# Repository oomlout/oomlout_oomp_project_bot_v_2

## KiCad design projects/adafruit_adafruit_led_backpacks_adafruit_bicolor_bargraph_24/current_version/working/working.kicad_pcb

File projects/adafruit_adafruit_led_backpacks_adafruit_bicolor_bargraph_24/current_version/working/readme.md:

# adafruit_led_backpacks
 
## summary 
* id: adafruit_adafruit_led_backpacks_adafruit_bicolor_bargraph_24
* user: adafruit
* name: adafruit_led_backpacks
* board: adafruit_bicolor_bargraph_24
* repo: https://github.com/adafruit/Adafruit-LED-Backpacks

* src_file_repo_sch: 
* src_file_repo_sch_link: https://github.com/adafruit/Adafruit-LED-Backpacks/tree/master/
* full details link: https://github.com/oomlout/oomlout_oomp_project_bot_v_2/tree/main/projects/adafruit_adafruit_led_backpacks_adafruit_bicolor_bargraph_24/current_version/working  

## schematic  
  
[schematic (pdf)](working_schematic.pdf) 

## pcb  

[board (pdf)](working.pdf)  

## working_bom
| Id | Designator | Footprint | Quantity | Designation | Supplier and ref |  | None | 
| --- | --- | --- | --- | --- | --- | --- | --- | 
| 1 | JP1 | 1X05_ROUND_70 | 1 |  |  |  | [''] | 
| 2 | D1,D3 | SOD-323F | 2 | CUS530 |  |  | [''] | 
| 3 | A0,A1,A2 | SOLDERJUMPER_REFLOW_NOPASTE | 3 |  |  |  | [''] | 
| 4 | R4,R3,R5,R6 | 0603-NO | 4 | 47K |  |  | [''] | 
| 5 | U$2,U$1 | FIDUCIAL_1MM | 2 | FIDUCIAL |  |  | [''] | 
| 6 | U2 | SOP28_300MIL_SKINNY | 1 | HT16K33 |  |  | [''] | 
| 7 | U$6,U$7 | STEMMAQT | 2 |  |  |  | [''] | 
| 8 | @HOLE0,@HOLE2,@HOLE3,@HOLE1 |  | 4 |  |  |  | [''] | 
| 9 | R2,R1 | 0603-NO | 2 | 10K |  |  | [''] | 
| 10 | U$3 | ADAFRUIT_5MM | 1 |  |  |  | [''] | 
| 11 | CONN1,CONN2 | JST_SH4_RA | 2 | STEMMA_I2C_QTRA |  |  | [''] | 
| 12 | D2 | CHIPLED_0603_NOOUTLINE | 1 | GREEN |  |  | [''] | 
| 13 | C1 | 0805-NO | 1 | 10uF |  |  | [''] | 
| 14 | LEDJMP0 | SOLDERJUMPER_CLOSEDWIRE | 1 |  |  |  | [''] | 
| 15 | U$8 | PCBFEAT-REV-040 | 1 |  |  |  | [''] | 
| 16 | LED1,LED2 | SEGMENT_STARTBUST_DUAL_KWA-541CBB | 2 |  |  |  | [''] | 

## bom_schematic
| Ref | Qnty | Value | Cmp name | Footprint | Description | Vendor | DNP | 
| --- | --- | --- | --- | --- | --- | --- | --- | 
| A0, A1, A2 | 3 | SOLDERJUMPERREFLOW_NOPASTE | SOLDERJUMPERREFLOW_NOPASTE | working:SOLDERJUMPER_REFLOW_NOPASTE |  |  |  | 
| C1 | 1 | 10uF | CAP_CERAMIC0805-NOOUTLINE | working:0805-NO |  |  |  | 
| CONN1, CONN2 | 2 | STEMMA_I2C_QTRA | STEMMA_I2C_QTRA | working:JST_SH4_RA |  |  |  | 
| D1, D3 | 2 | CUS530 | DIODESOD-323F | working:SOD-323F |  |  |  | 
| D2 | 1 | GREEN | LED0603_NOOUTLINE | working:CHIPLED_0603_NOOUTLINE |  |  |  | 
| JP1 | 1 | HEADER-1X570MIL | HEADER-1X570MIL | working:1X05_ROUND_70 |  |  |  | 
| LED1, LED2 | 2 | DISP_SEGMENT_STARBURST_DUAL_COMMONCATHODE | DISP_SEGMENT_STARBURST_DUAL_COMMONCATHODE | working:SEGMENT_STARTBUST_DUAL_KWA-541CBB |  |  |  | 
| LEDJMP0 | 1 | SOLDERJUMPERCLOSED | SOLDERJUMPERCLOSED | working:SOLDERJUMPER_CLOSEDWIRE |  |  |  | 
| R1, R2 | 2 | 10K | RESISTOR_0603_NOOUT | working:0603-NO |  |  |  | 
| R3, R4, R5, R6 | 4 | 47K | RESISTOR_0603_NOOUT | working:0603-NO |  |  |  | 
| U2 | 1 | HT16K33 | HT16K33_SOP28_SKINNY | working:SOP28_300MIL_SKINNY |  |  |  | 
| U$1, U$2 | 2 | FIDUCIAL | FIDUCIAL | working:FIDUCIAL_1MM |  |  |  |

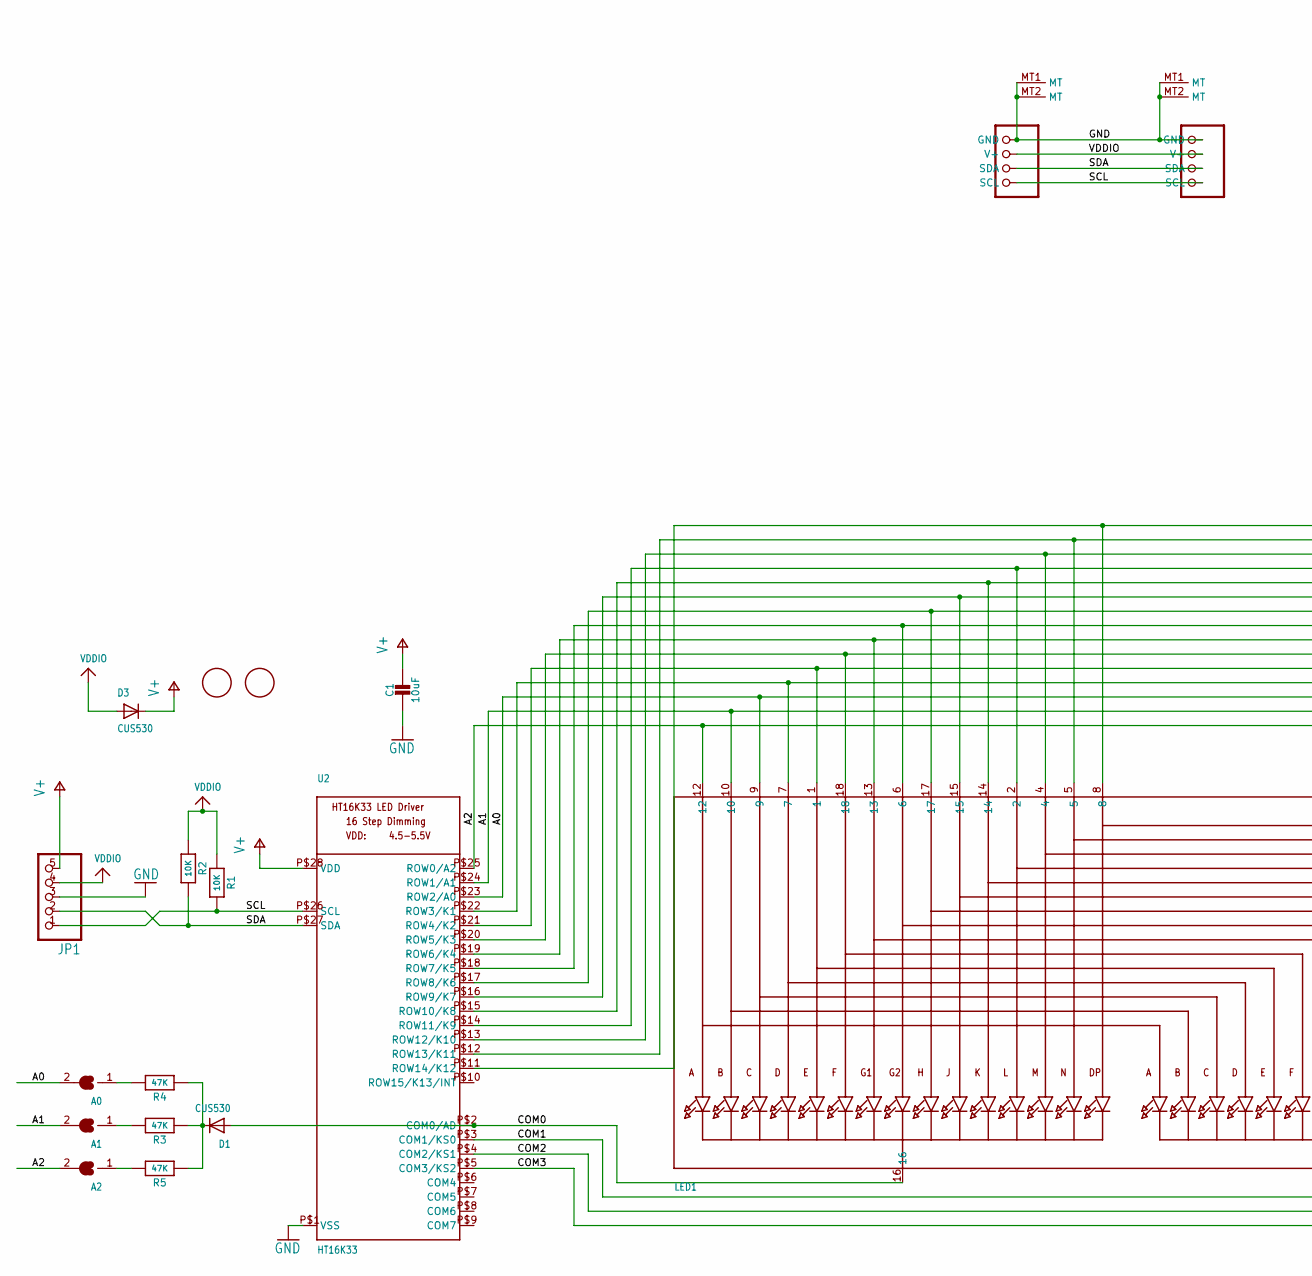
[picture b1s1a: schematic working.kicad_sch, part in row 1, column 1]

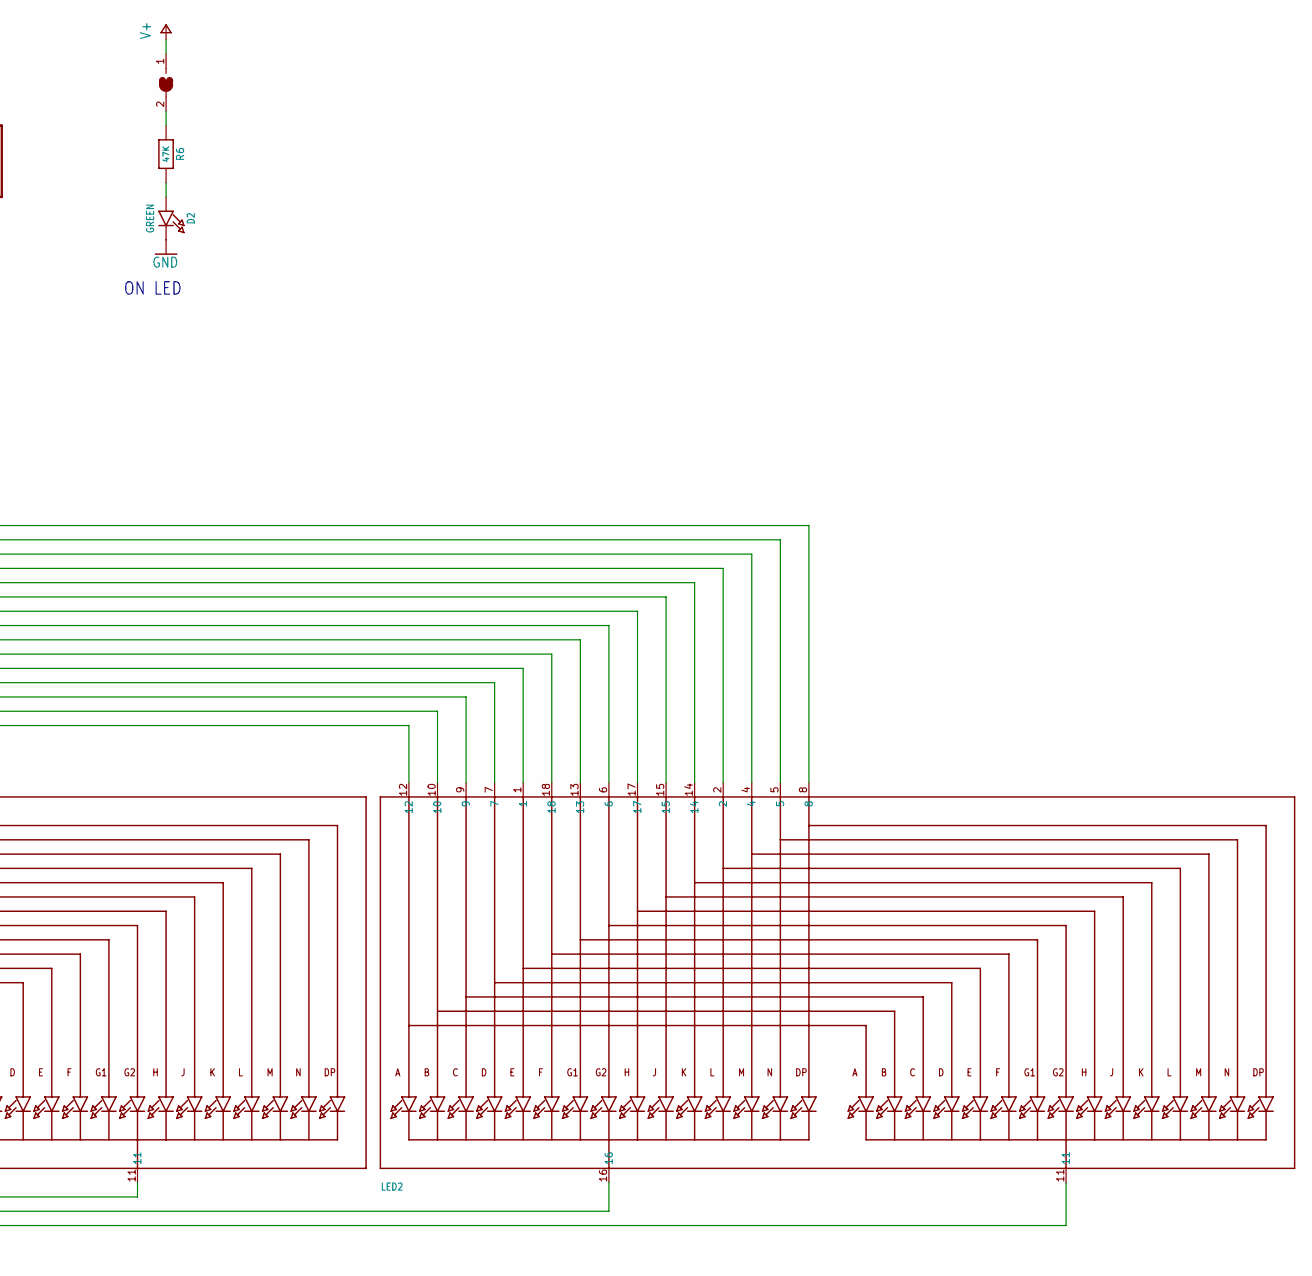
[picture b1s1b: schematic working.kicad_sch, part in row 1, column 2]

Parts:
A0, A1, A2: SOLDERJUMPERREFLOW_NOPASTE; SOLDERJUMPER_REFLOW_NOPASTE
C1: 10uF; 0805-NO
CONN1, CONN2: STEMMA_I2C_QTRA; JST_SH4_RA
D1, D3: CUS530; SOD-323F
D2: GREEN; CHIPLED_0603_NOOUTLINE
JP1: HEADER-1X570MIL; 1X05_ROUND_70
LED1, LED2: DISP_SEGMENT_STARBURST_DUAL_COMMONCATHODE; SEGMENT_STARTBUST_DUAL_KWA-541CBB
LEDJMP0: SOLDERJUMPERCLOSED; SOLDERJUMPER_CLOSEDWIRE
R1, R2: 10K; 0603-NO
R3, R4, R5, R6: 47K; 0603-NO
U2: HT16K33; SOP28_300MIL_SKINNY
U$1, U$2: FIDUCIAL; FIDUCIAL_1MM

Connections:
A0: A0.2, LED1.9, LED2.9, U2.P$23 (ROW2/A0)
A1: A1.2, LED1.10, LED2.10, U2.P$24 (ROW1/A1)
A2: A2.2, LED1.12, LED2.12, U2.P$25 (ROW0/A2)
COM0: D1.A, LED1.16, U2.P$2 (COM0/AD)
COM1: LED1.11, U2.P$3 (COM1/KS0)
COM2: LED2.16, U2.P$4 (COM2/KS1)
COM3: LED2.11, U2.P$5 (COM3/KS2)
GND: C1.2, CONN1.1 (GND), CONN1.MT1 (MT), CONN1.MT2 (MT), CONN2.1 (GND), CONN2.MT1 (MT), CONN2.MT2 (MT), D2.C, JP1.3, U2.P$1 (VSS)
unnamed: D1.C, R3.1, R4.1, R5.1
unnamed: D2.A, R6.2
unnamed: LED1.17, LED2.17, U2.P$17 (ROW8/K6)
unnamed: LED1.15, LED2.15, U2.P$16 (ROW9/K7)
unnamed: LED1.14, LED2.14, U2.P$15 (ROW10/K8)
unnamed: A2.1, R5.2
unnamed: LED1.2, LED2.2, U2.P$14 (ROW11/K9)
unnamed: LED1.4, LED2.4, U2.P$13 (ROW12/K10)
unnamed: LED1.7, LED2.7, U2.P$22 (ROW3/K1)
unnamed: LED1.1, LED2.1, U2.P$21 (ROW4/K2)
unnamed: LED1.18, LED2.18, U2.P$20 (ROW5/K3)
unnamed: LED1.13, LED2.13, U2.P$19 (ROW6/K4)
unnamed: LED1.5, LED2.5, U2.P$12 (ROW13/K11)
unnamed: LED1.8, LED2.8, U2.P$11 (ROW14/K12)
unnamed: LED1.6, LED2.6, U2.P$18 (ROW7/K5)
unnamed: LEDJMP0.2, R6.1
unnamed: A1.1, R3.2
unnamed: A0.1, R4.2
SCL: CONN1.4 (SCL), CONN2.4 (SCL), JP1.1, R1.2, U2.P$26 (SCL)
SDA: CONN1.3 (SDA), CONN2.3 (SDA), JP1.2, R2.2, U2.P$27 (SDA)
V+: C1.1, D3.C, JP1.5, LEDJMP0.1, U2.P$28 (VDD)
VDDIO: CONN1.2 (V+), CONN2.2 (V+), D3.A, JP1.4, R1.1, R2.1

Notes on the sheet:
ON LED

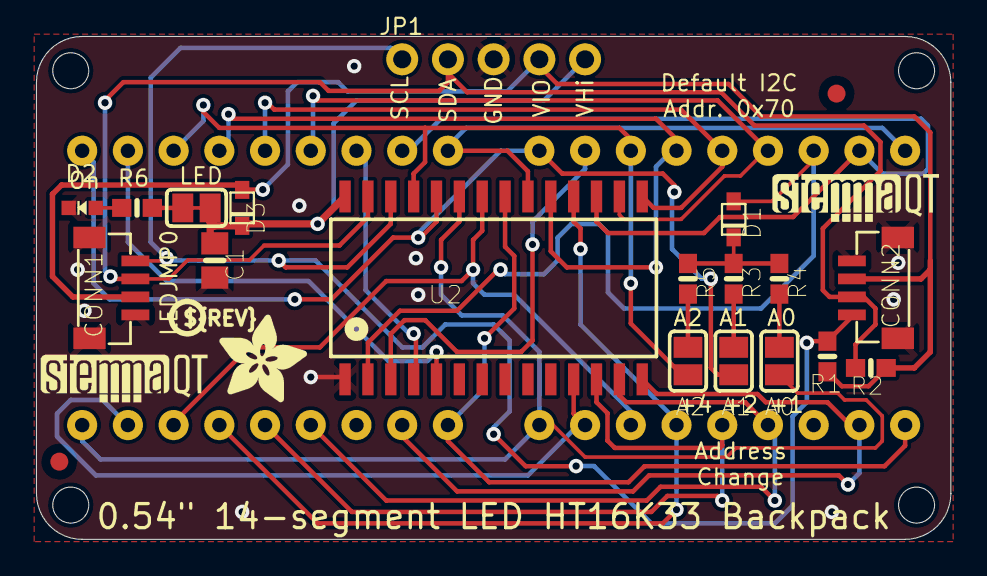
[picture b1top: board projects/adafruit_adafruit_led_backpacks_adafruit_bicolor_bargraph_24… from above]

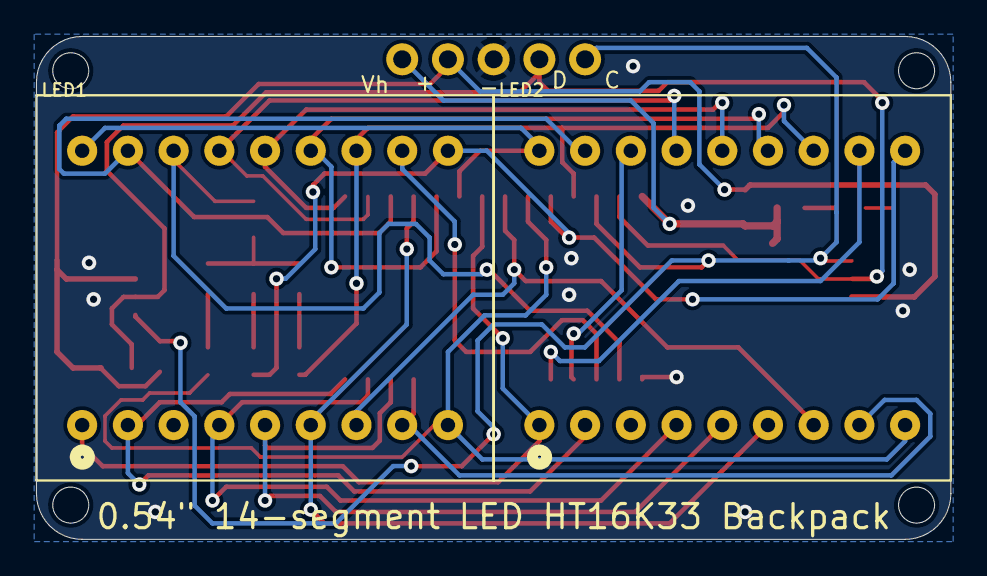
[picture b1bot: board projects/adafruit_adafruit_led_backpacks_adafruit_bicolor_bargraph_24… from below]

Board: 16 copper layers, 50.8 x 27.9 mm, 30 parts (2 on the bottom side), 30 nets.

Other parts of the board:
@HOLE0, @HOLE1, @HOLE2, @HOLE3: (no value)
U$3: ADAFRUIT_5MM
U$6, U$7: STEMMAQT
U$8: PCBFEAT-REV-040

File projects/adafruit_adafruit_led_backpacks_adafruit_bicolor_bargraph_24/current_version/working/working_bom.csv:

"Id";"Designator";"Footprint";"Quantity";"Designation";"Supplier and ref";
1;"JP1";"1X05_ROUND_70";1;"";;;
2;"D1,D3";"SOD-323F";2;"CUS530";;;
3;"A0,A1,A2";"SOLDERJUMPER_REFLOW_NOPASTE";3;"";;;
4;"R4,R3,R5,R6";"0603-NO";4;"47K";;;
5;"U$2,U$1";"FIDUCIAL_1MM";2;"FIDUCIAL";;;
6;"U2";"SOP28_300MIL_SKINNY";1;"HT16K33";;;
7;"U$6,U$7";"STEMMAQT";2;"";;;
8;"@HOLE0,@HOLE2,@HOLE3,@HOLE1";"";4;"";;;
9;"R2,R1";"0603-NO";2;"10K";;;
10;"U$3";"ADAFRUIT_5MM";1;"";;;
11;"CONN1,CONN2";"JST_SH4_RA";2;"STEMMA_I2C_QTRA";;;
12;"D2";"CHIPLED_0603_NOOUTLINE";1;"GREEN";;;
13;"C1";"0805-NO";1;"10uF";;;
14;"LEDJMP0";"SOLDERJUMPER_CLOSEDWIRE";1;"";;;
15;"U$8";"PCBFEAT-REV-040";1;"";;;
16;"LED1,LED2";"SEGMENT_STARTBUST_DUAL_KWA-541CBB";2;"";;;

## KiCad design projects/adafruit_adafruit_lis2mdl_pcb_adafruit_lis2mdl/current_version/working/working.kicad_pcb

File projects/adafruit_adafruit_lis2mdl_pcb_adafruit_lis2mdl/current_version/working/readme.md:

# adafruit_lis2mdl_pcb
 
## summary 
* id: adafruit_adafruit_lis2mdl_pcb_adafruit_lis2mdl
* user: adafruit
* name: adafruit_lis2mdl_pcb
* board: adafruit_lis2mdl
* repo: https://github.com/adafruit/Adafruit-LIS2MDL-PCB

* src_file_repo_sch: 
* src_file_repo_sch_link: https://github.com/adafruit/Adafruit-LIS2MDL-PCB/tree/master/
* full details link: https://github.com/oomlout/oomlout_oomp_project_bot_v_2/tree/main/projects/adafruit_adafruit_lis2mdl_pcb_adafruit_lis2mdl/current_version/working  

## schematic  
  
[schematic (pdf)](working_schematic.pdf) 

## pcb  

[board (pdf)](working.pdf)  

## working_bom
| Id | Designator | Footprint | Quantity | Designation | Supplier and ref |  | None | 
| --- | --- | --- | --- | --- | --- | --- | --- | 
| 1 | C4,C1 | 0603-NO | 2 | 0.1uF |  |  | [''] | 
| 2 | C5 | 0603-NO | 1 | 1uF |  |  | [''] | 
| 3 | U$11 | ADAFRUIT_3.5MM | 1 |  |  |  | [''] | 
| 4 | JP1 | 1X07_ROUND_70 | 1 |  |  |  | [''] | 
| 5 | @HOLE0,@HOLE1 |  | 2 |  |  |  | [''] | 
| 6 | FID4,FID3 | FIDUCIAL_1MM | 2 | FIDUCIAL_1MM |  |  | [''] | 
| 7 | D2 | SOD-323 | 1 | 1N4148 |  |  | [''] | 
| 8 | IC1 | LGA12_2X2MM | 1 | LIS2MDL |  |  | [''] | 
| 9 | U$1,U$17 | MOUNTINGHOLE_2.5_PLATED | 2 | MOUNTINGHOLE2.5 |  |  | [''] | 
| 10 | R3 | RESPACK_4X0603 | 1 | 10K |  |  | [''] | 
| 11 | R2,R4,R1 | 0603-NO | 3 | 10K |  |  | [''] | 
| 12 | CONN3,CONN4 | JST_SH4 | 2 | STEMMA_I2C_QT |  |  | [''] | 
| 13 | D1 | CHIPLED_0603_NOOUTLINE | 1 | GREEN |  |  | [''] | 
| 14 | C2,C3 | 0805-NO | 2 | 10uF |  |  | [''] | 
| 15 | Q2 | SOT363 | 1 | BSS138 |  |  | [''] | 
| 16 | U2 | SOT23-5 | 1 | AP2112K-3.3 |  |  | [''] | 
| 17 | U$25 | PCBFEAT-REV-040 | 1 |  |  |  | [''] | 
| 18 | U$30,U$31 | STEMMAQT | 2 |  |  |  | [''] | 

## bom_schematic
| Ref | Qnty | Value | Cmp name | Footprint | Description | Vendor | DNP | 
| --- | --- | --- | --- | --- | --- | --- | --- | 
| C1, C4 | 2 | 0.1uF | CAP_CERAMIC0603_NO | working:0603-NO |  |  |  | 
| C2, C3 | 2 | 10uF | CAP_CERAMIC0805-NOOUTLINE | working:0805-NO |  |  |  | 
| C5 | 1 | 1uF | CAP_CERAMIC0603_NO | working:0603-NO |  |  |  | 
| CONN3, CONN4 | 2 | STEMMA_I2C_QT | STEMMA_I2C_QT | working:JST_SH4 |  |  |  | 
| D1 | 1 | GREEN | LED0603_NOOUTLINE | working:CHIPLED_0603_NOOUTLINE |  |  |  | 
| D2 | 1 | 1N4148 | DIODESOD-323 | working:SOD-323 |  |  |  | 
| FID3, FID4 | 2 | FIDUCIAL_1MM | FIDUCIAL_1MM | working:FIDUCIAL_1MM |  |  |  | 
| IC1 | 1 | LIS2MDL | LIS2MDL | working:LGA12_2X2MM |  |  |  | 
| JP1 | 1 | HEADER-1X770MIL | HEADER-1X770MIL | working:1X07_ROUND_70 |  |  |  | 
| Q2 | 1 | BSS138 | MOSFET-N_DUAL | working:SOT363 |  |  |  | 
| R1, R2, R4 | 3 | 10K | RESISTOR_0603_NOOUT | working:0603-NO |  |  |  | 
| R3 | 1 | 10K | RESISTOR_4PACK | working:RESPACK_4X0603 |  |  |  | 
| U2 | 1 | AP2112K-3.3 | VREG_SOT23-5 | working:SOT23-5 |  |  |  | 
| U$1, U$17 | 2 | MOUNTINGHOLE2.5 | MOUNTINGHOLE2.5 | working:MOUNTINGHOLE_2.5_PLATED |  |  |  | 

## mounting_holes
| x | y | package | value | ref | size | 
| --- | --- | --- | --- | --- | --- | 
| 0.0 | 0.0 | MOUNTINGHOLE_2.5_PLATED | MOUNTINGHOLE2.5 | U$1 | m3 | 
| 20.32 | 0.0 | MOUNTINGHOLE_2.5_PLATED | MOUNTINGHOLE2.5 | U$17 | m3 |

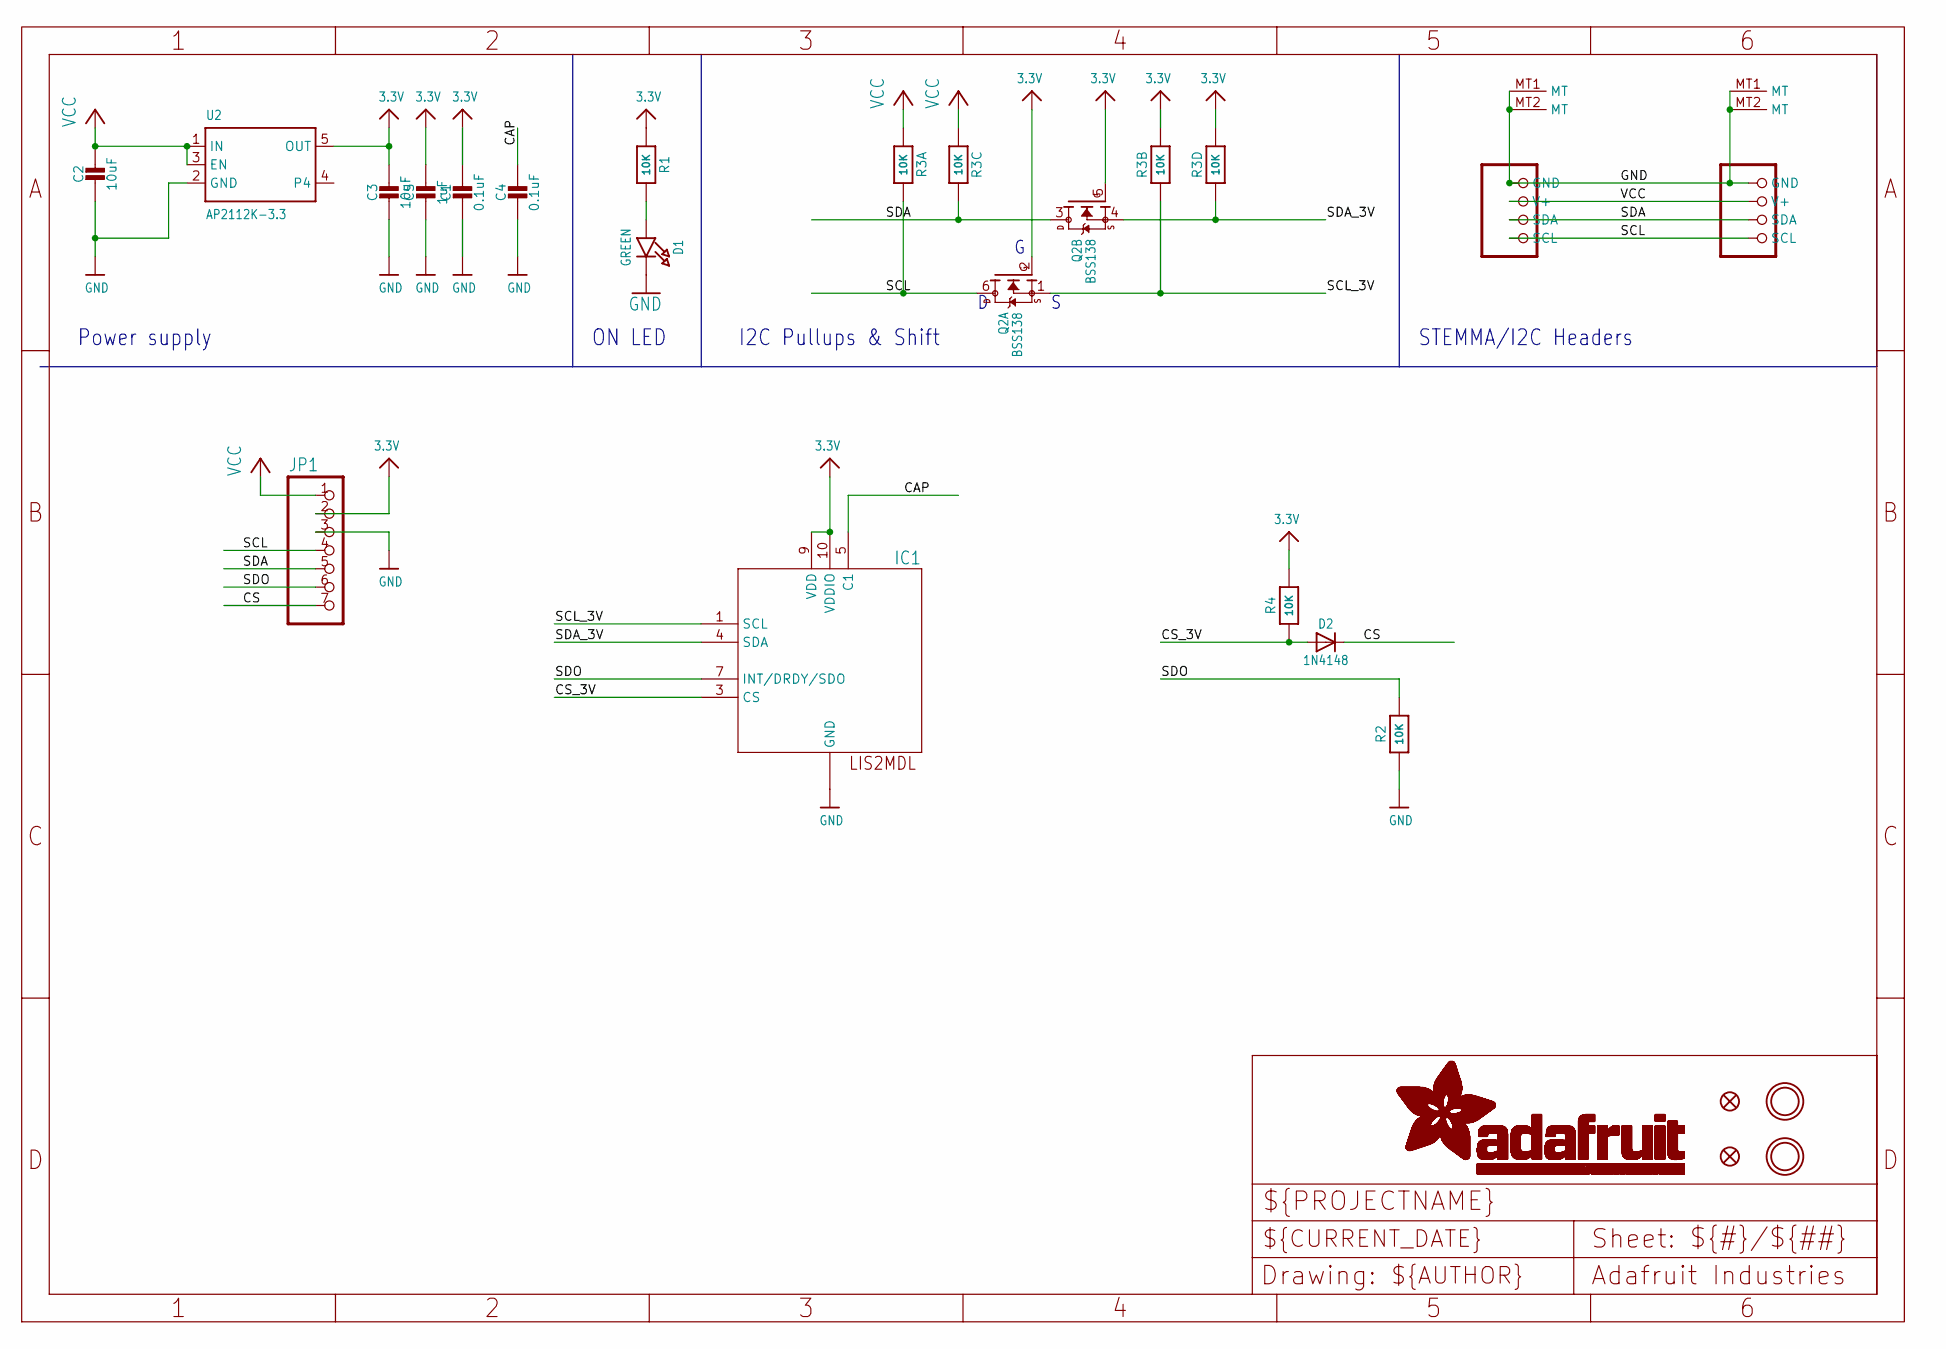
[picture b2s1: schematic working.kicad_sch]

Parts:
C1, C4: 0.1uF; 0603-NO
C2, C3: 10uF; 0805-NO
C5: 1uF; 0603-NO
CONN3, CONN4: STEMMA_I2C_QT; JST_SH4
D1: GREEN; CHIPLED_0603_NOOUTLINE
D2: 1N4148; SOD-323
FID3, FID4: FIDUCIAL_1MM
IC1: LIS2MDL; LGA12_2X2MM
JP1: HEADER-1X770MIL; 1X07_ROUND_70
Q2: BSS138; SOT363
R1, R2, R4: 10K; 0603-NO
R3: 10K; RESPACK_4X0603
U2: AP2112K-3.3; SOT23-5
U$1, U$17: MOUNTINGHOLE2.5; MOUNTINGHOLE_2.5_PLATED

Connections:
3.3V: C1.1, C3.1, C5.1, IC1.9 (VDD), IC1.10 (VDDIO), JP1.2, Q2.2 (G), Q2.5 (G), R1.1, R3.2 (1), R3.4 (1), R4.2, U2.5 (OUT)
CAP: C4.1, IC1.5 (C1)
CS: D2.C, JP1.7
CS_3V: D2.A, IC1.3 (CS), R4.1
GND: C1.2, C2.2, C3.2, C4.2, C5.2, CONN3.1 (GND), CONN3.MT1 (MT), CONN3.MT2 (MT), CONN4.1 (GND), CONN4.MT1 (MT), CONN4.MT2 (MT), D1.C, IC1.2 (GND), IC1.6 (GND), IC1.8 (GND), IC1.11 (GND), IC1.12 (GND), JP1.3, R2.1, U2.2 (GND)
unnamed: D1.A, R1.2
SCL: CONN3.4 (SCL), CONN4.4 (SCL), JP1.4, Q2.6 (D), R3.8 (2)
SCL_3V: IC1.1 (SCL), Q2.1 (S), R3.7 (2)
SDA: CONN3.3 (SDA), CONN4.3 (SDA), JP1.5, Q2.3 (D), R3.6 (2)
SDA_3V: IC1.4 (SDA), Q2.4 (S), R3.5 (2)
SDO: IC1.7 (INT/DRDY/SDO), JP1.6, R2.2
VCC: C2.1, CONN3.2 (V+), CONN4.2 (V+), JP1.1, R3.1, R3.3 (1), U2.1 (IN), U2.3 (EN)

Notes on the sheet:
ON LED
Power supply
STEMMA/I2C Headers
I2C Pullups & Shift

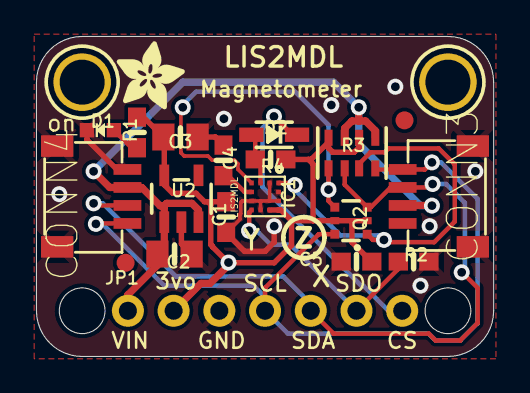
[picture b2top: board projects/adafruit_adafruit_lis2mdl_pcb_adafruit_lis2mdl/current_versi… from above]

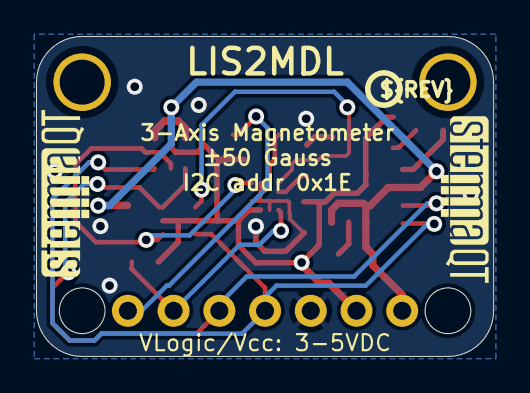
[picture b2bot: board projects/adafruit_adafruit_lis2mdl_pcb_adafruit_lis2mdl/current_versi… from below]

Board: 2 copper layers, 25.4 x 17.8 mm, 27 parts (3 on the bottom side), 12 nets.

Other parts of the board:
@HOLE0, @HOLE1: (no value)
U$11: ADAFRUIT_3.5MM
U$25: PCBFEAT-REV-040
U$30, U$31: STEMMAQT

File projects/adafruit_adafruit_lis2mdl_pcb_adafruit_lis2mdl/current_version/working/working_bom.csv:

"Id";"Designator";"Footprint";"Quantity";"Designation";"Supplier and ref";
1;"C4,C1";"0603-NO";2;"0.1uF";;;
2;"C5";"0603-NO";1;"1uF";;;
3;"U$11";"ADAFRUIT_3.5MM";1;"";;;
4;"JP1";"1X07_ROUND_70";1;"";;;
5;"@HOLE0,@HOLE1";"";2;"";;;
6;"FID4,FID3";"FIDUCIAL_1MM";2;"FIDUCIAL_1MM";;;
7;"D2";"SOD-323";1;"1N4148";;;
8;"IC1";"LGA12_2X2MM";1;"LIS2MDL";;;
9;"U$1,U$17";"MOUNTINGHOLE_2.5_PLATED";2;"MOUNTINGHOLE2.5";;;
10;"R3";"RESPACK_4X0603";1;"10K";;;
11;"R2,R4,R1";"0603-NO";3;"10K";;;
12;"CONN3,CONN4";"JST_SH4";2;"STEMMA_I2C_QT";;;
13;"D1";"CHIPLED_0603_NOOUTLINE";1;"GREEN";;;
14;"C2,C3";"0805-NO";2;"10uF";;;
15;"Q2";"SOT363";1;"BSS138";;;
16;"U2";"SOT23-5";1;"AP2112K-3.3";;;
17;"U$25";"PCBFEAT-REV-040";1;"";;;
18;"U$30,U$31";"STEMMAQT";2;"";;;

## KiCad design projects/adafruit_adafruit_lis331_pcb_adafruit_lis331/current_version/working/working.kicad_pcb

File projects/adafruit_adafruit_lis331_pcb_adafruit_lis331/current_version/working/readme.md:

# adafruit_lis331_pcb
 
## summary 
* id: adafruit_adafruit_lis331_pcb_adafruit_lis331
* user: adafruit
* name: adafruit_lis331_pcb
* board: adafruit_lis331
* repo: https://github.com/adafruit/Adafruit-LIS331-PCB

* src_file_repo_sch: 
* src_file_repo_sch_link: https://github.com/adafruit/Adafruit-LIS331-PCB/tree/master/
* full details link: https://github.com/oomlout/oomlout_oomp_project_bot_v_2/tree/main/projects/adafruit_adafruit_lis331_pcb_adafruit_lis331/current_version/working  

## schematic  
  
[schematic (pdf)](working_schematic.pdf) 

## pcb  

[board (pdf)](working.pdf)  

## working_bom
| Id | Designator | Footprint | Quantity | Designation | Supplier and ref |  | None | 
| --- | --- | --- | --- | --- | --- | --- | --- | 
| 1 | U$12 | ADAFRUIT_2.5MM | 1 |  |  |  | [''] | 
| 2 | U$17,U$21,U$1,U$19 | MOUNTINGHOLE_2.5_PLATED | 4 | MOUNTINGHOLE2.5 |  |  | [''] | 
| 3 | JP2,JP3 | 1X06_ROUND_70 | 2 |  |  |  | [''] | 
| 4 | CONN3,CONN4 | JST_SH4 | 2 | STEMMA_I2C_QT |  |  | [''] | 
| 5 | R1,R3 | RESPACK_4X0603 | 2 | 10K |  |  | [''] | 
| 6 | U2 | SOT23-5 | 1 | AP2112K-3.3 |  |  | [''] | 
| 7 | D1 | CHIPLED_0603_NOOUTLINE | 1 | GREEN |  |  | [''] | 
| 8 | C2,C3 | 0805-NO | 2 | 10uF |  |  | [''] | 
| 9 | FID3,FID4 | FIDUCIAL_1MM | 2 | FIDUCIAL_1MM |  |  | [''] | 
| 10 | Q2 | SOT363 | 1 | BSS138 |  |  | [''] | 
| 11 | C1 | 0603-NO | 1 | 0.1uF |  |  | [''] | 
| 12 | D2 | SOD-323 | 1 | 1N4148 |  |  | [''] | 
| 13 | U1 | LGA16_3X3MM | 1 | LIS3DHTR |  |  | [''] | 
| 14 | U$30,U$31 | STEMMAQT | 2 |  |  |  | [''] | 
| 15 | SJ1 | SOLDERJUMPER_ARROW_NOPASTE | 1 |  |  |  | [''] | 
| 16 | U$25 | PCBFEAT-REV-040 | 1 |  |  |  | [''] | 

## bom_schematic
| Ref | Qnty | Value | Cmp name | Footprint | Description | Vendor | DNP | 
| --- | --- | --- | --- | --- | --- | --- | --- | 
| C1 | 1 | 0.1uF | CAP_CERAMIC0603_NO | working:0603-NO |  |  |  | 
| C2, C3 | 2 | 10uF | CAP_CERAMIC0805-NOOUTLINE | working:0805-NO |  |  |  | 
| CONN3, CONN4 | 2 | STEMMA_I2C_QT | STEMMA_I2C_QT | working:JST_SH4 |  |  |  | 
| D1 | 1 | GREEN | LED0603_NOOUTLINE | working:CHIPLED_0603_NOOUTLINE |  |  |  | 
| D2 | 1 | 1N4148 | DIODESOD-323 | working:SOD-323 |  |  |  | 
| FID3, FID4 | 2 | FIDUCIAL_1MM | FIDUCIAL_1MM | working:FIDUCIAL_1MM |  |  |  | 
| JP2, JP3 | 2 | HEADER-1X670MIL | HEADER-1X670MIL | working:1X06_ROUND_70 |  |  |  | 
| Q2 | 1 | BSS138 | MOSFET-N_DUAL | working:SOT363 |  |  |  | 
| R1, R3 | 2 | 10K | RESISTOR_4PACK | working:RESPACK_4X0603 |  |  |  | 
| SJ1 | 1 | SOLDERJUMPER | SOLDERJUMPER | working:SOLDERJUMPER_ARROW_NOPASTE |  |  |  | 
| U1 | 1 | LIS3DHTR | ACCEL_LIS3DHTR | working:LGA16_3X3MM |  |  |  | 
| U2 | 1 | AP2112K-3.3 | VREG_SOT23-5 | working:SOT23-5 |  |  |  | 
| U$1, U$17, U$19, U$21 | 4 | MOUNTINGHOLE2.5 | MOUNTINGHOLE2.5 | working:MOUNTINGHOLE_2.5_PLATED |  |  |  | 

## mounting_holes
| x | y | package | value | ref | size | 
| --- | --- | --- | --- | --- | --- | 
| 0.0 | 12.7 | MOUNTINGHOLE_2.5_PLATED | MOUNTINGHOLE2.5 | U$1 | m3 | 
| 20.32 | 12.7 | MOUNTINGHOLE_2.5_PLATED | MOUNTINGHOLE2.5 | U$17 | m3 | 
| 0.0 | 0.0 | MOUNTINGHOLE_2.5_PLATED | MOUNTINGHOLE2.5 | U$19 | m3 | 
| 20.32 | 0.0 | MOUNTINGHOLE_2.5_PLATED | MOUNTINGHOLE2.5 | U$21 | m3 |

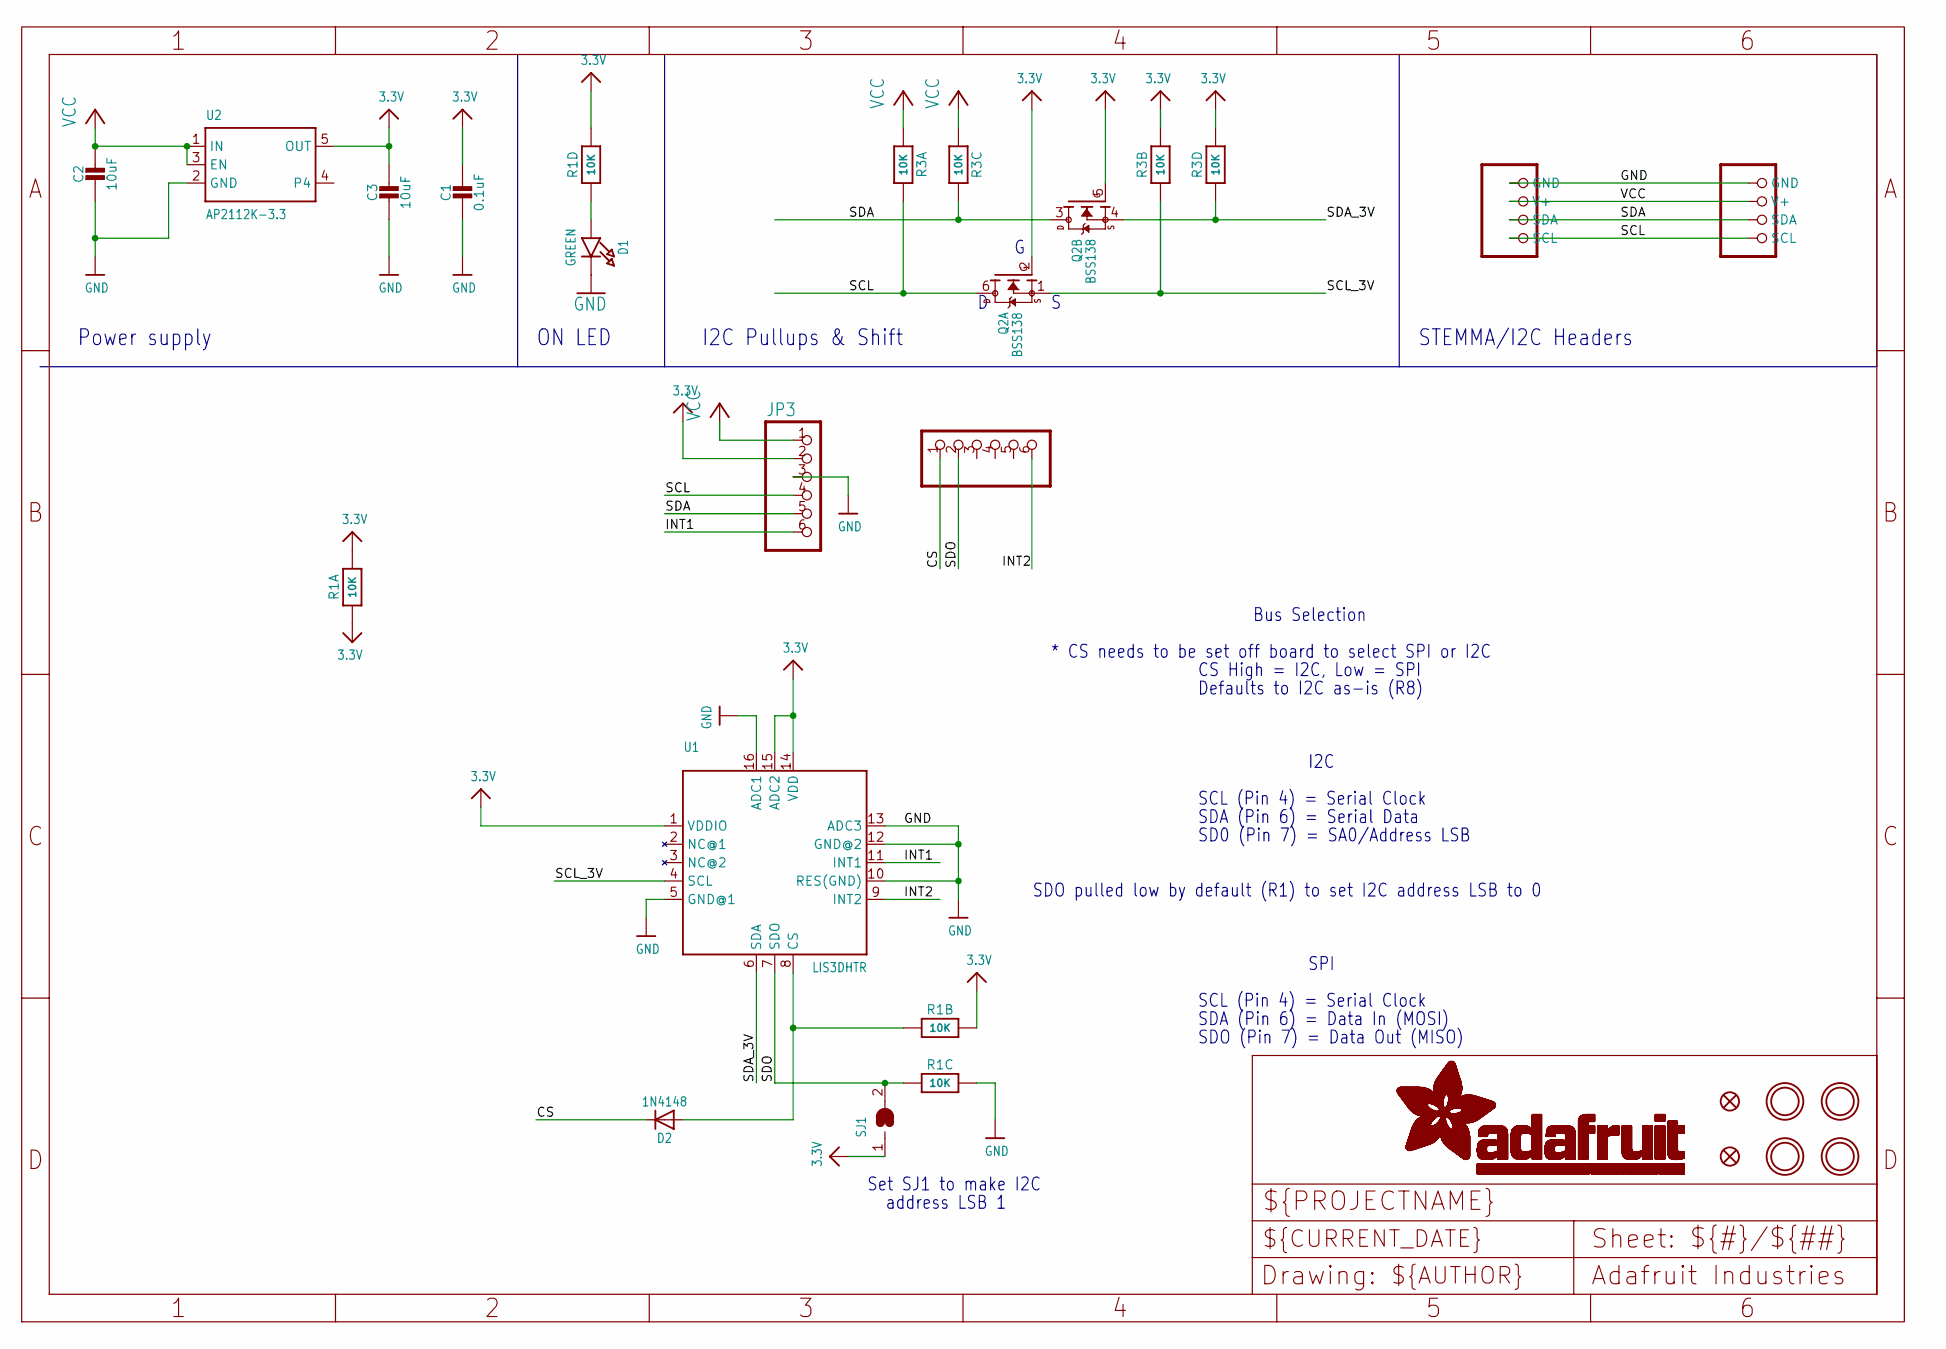
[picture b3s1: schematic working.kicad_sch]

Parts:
C1: 0.1uF; 0603-NO
C2, C3: 10uF; 0805-NO
CONN3, CONN4: STEMMA_I2C_QT; JST_SH4
D1: GREEN; CHIPLED_0603_NOOUTLINE
D2: 1N4148; SOD-323
FID3, FID4: FIDUCIAL_1MM
JP2, JP3: HEADER-1X670MIL; 1X06_ROUND_70
Q2: BSS138; SOT363
R1, R3: 10K; RESPACK_4X0603
SJ1: SOLDERJUMPER; SOLDERJUMPER_ARROW_NOPASTE
U1: LIS3DHTR; LGA16_3X3MM
U2: AP2112K-3.3; SOT23-5
U$1, U$17, U$19, U$21: MOUNTINGHOLE2.5; MOUNTINGHOLE_2.5_PLATED

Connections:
3.3V: C1.1, C3.1, JP3.2, Q2.2 (G), Q2.5 (G), R1.1, R1.5 (2), R1.7 (2), R1.8 (2), R3.2 (1), R3.4 (1), SJ1.1, U1.1 (VDDIO), U1.14 (VDD), U1.15 (ADC2), U2.5 (OUT)
CS: D2.C, JP2.1
GND: C1.2, C2.2, C3.2, CONN3.1 (GND), CONN4.1 (GND), D1.C, JP3.3, R1.6 (2), U1.5 (GND@1), U1.10 (RES(GND)), U1.12 (GND@2), U1.13 (ADC3), U1.16 (ADC1), U2.2 (GND)
INT1: JP3.6, U1.11 (INT1)
INT2: JP2.6, U1.9 (INT2)
unnamed: D1.A, R1.4 (1)
unnamed: D2.A, R1.2 (1), U1.8 (CS)
SCL: CONN3.4 (SCL), CONN4.4 (SCL), JP3.4, Q2.6 (D), R3.8 (2)
SCL_3V: Q2.1 (S), R3.7 (2), U1.4 (SCL)
SDA: CONN3.3 (SDA), CONN4.3 (SDA), JP3.5, Q2.3 (D), R3.6 (2)
SDA_3V: Q2.4 (S), R3.5 (2), U1.6 (SDA)
SDO: JP2.2, R1.3 (1), SJ1.2, U1.7 (SDO)
VCC: C2.1, CONN3.2 (V+), CONN4.2 (V+), JP3.1, R3.1, R3.3 (1), U2.1 (IN), U2.3 (EN)

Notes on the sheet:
address LSB 1
SDO (Pin 7) = Data Out (MISO)
SDA (Pin 6) = Data In (MOSI)
SPI
Bus Selection
SDA (Pin 6) = Serial Data
CS High = I2C, Low = SPI
Set SJ1 to make I2C
ON LED
SCL (Pin 4) = Serial Clock
STEMMA/I2C Headers
* CS needs to be set off board to select SPI or I2C
I2C Pullups & Shift
Defaults to I2C as-is (R8)
I2C
SD0 (Pin 7) = SA0/Address LSB
SDO pulled low by default (R1) to set I2C address LSB to 0
Power supply

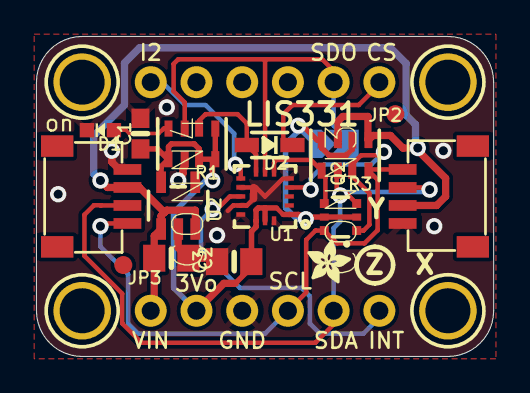
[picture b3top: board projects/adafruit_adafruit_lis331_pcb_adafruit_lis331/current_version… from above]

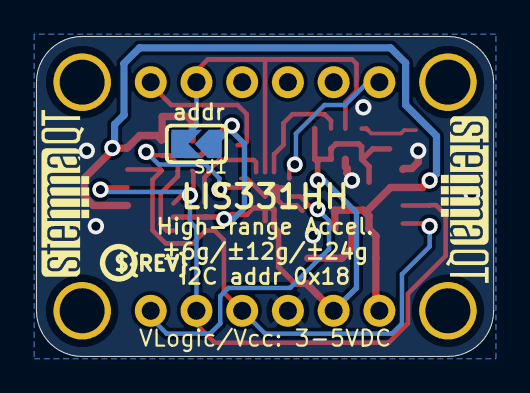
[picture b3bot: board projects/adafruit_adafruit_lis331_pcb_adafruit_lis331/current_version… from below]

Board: 2 copper layers, 25.4 x 17.8 mm, 25 parts (4 on the bottom side), 13 nets.

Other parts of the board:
U$12: ADAFRUIT_2.5MM
U$25: PCBFEAT-REV-040
U$30, U$31: STEMMAQT

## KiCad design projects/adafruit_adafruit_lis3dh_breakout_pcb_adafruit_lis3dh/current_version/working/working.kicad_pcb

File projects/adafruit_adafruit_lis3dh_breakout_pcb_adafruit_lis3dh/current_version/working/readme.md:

# adafruit_lis3dh_breakout_pcb
 
## summary 
* id: adafruit_adafruit_lis3dh_breakout_pcb_adafruit_lis3dh
* user: adafruit
* name: adafruit_lis3dh_breakout_pcb
* board: adafruit_lis3dh
* repo: https://github.com/adafruit/Adafruit-LIS3DH-Breakout-PCB

* src_file_repo_sch: 
* src_file_repo_sch_link: https://github.com/adafruit/Adafruit-LIS3DH-Breakout-PCB/tree/master/
* full details link: https://github.com/oomlout/oomlout_oomp_project_bot_v_2/tree/main/projects/adafruit_adafruit_lis3dh_breakout_pcb_adafruit_lis3dh/current_version/working  

## schematic  
  
[schematic (pdf)](working_schematic.pdf) 

## pcb  

[board (pdf)](working.pdf)  

## working_bom
| Id | Designator | Footprint | Quantity | Designation | Supplier and ref |  | None | 
| --- | --- | --- | --- | --- | --- | --- | --- | 
| 1 | R5,R2,R3,R4,R8,R1 | 0805-NO | 6 | 10K |  |  | [''] | 
| 2 | Q1,Q2 | SOT23-WIDE | 2 | BSS138 |  |  | [''] | 
| 3 | U$13,U$10 | MOUNTINGHOLE_2.5_PLATED | 2 | MOUNTINGHOLE2.5 |  |  | [''] | 
| 4 | FID2,FID1 | FIDUCIAL_1MM | 2 | FIDUCIAL" |  |  | [''] | 
| 5 | C1 | 0805_10MGAP | 1 | 0.1uF |  |  | [''] | 
| 6 | C2,C3 | 0805-NO | 2 | 10ÂµF |  |  | [''] | 
| 7 | U2 | SOT23-5 | 1 | MIC5225-3.3 |  |  | [''] | 
| 8 | D2 | SOD-323 | 1 | 1N4148 |  |  | [''] | 
| 9 | JP1 | 1X03_ROUND | 1 |  |  |  | [''] | 
| 10 | U1 | LGA16_3X3MM | 1 | LIS3DHTR |  |  | [''] | 
| 11 | U$9 | PCBFEAT-REV-040 | 1 |  |  |  | [''] | 
| 12 | JP2 | 1X08_ROUND_70 | 1 |  |  |  | [''] | 
| 13 | U$21 | ADAFRUIT_2.5MM | 1 |  |  |  | [''] | 
| 14 | U$22 | ADAFRUIT_5MM | 1 |  |  |  | [''] | 

## bom_schematic
| Ref | Qnty | Value | Cmp name | Footprint | Description | Vendor | DNP | 
| --- | --- | --- | --- | --- | --- | --- | --- | 
| C1 | 1 | 0.1uF | CAP_CERAMIC0805_10MGAP | working:0805_10MGAP |  |  |  | 
| C2, C3 | 2 | 10ÂµF | CAP_CERAMIC0805-NOOUTLINE | working:0805-NO |  |  |  | 
| D2 | 1 | 1N4148 | DIODESOD-323 | working:SOD-323 |  |  |  | 
| FID1, FID2 | 2 | FIDUCIAL"" | FIDUCIAL{dblquote}{dblquote} | working:FIDUCIAL_1MM |  |  |  | 
| JP1 | 1 | HEADER-1X3ROUND | HEADER-1X3ROUND | working:1X03_ROUND |  |  |  | 
| JP2 | 1 | HEADER-1X870MIL | HEADER-1X870MIL | working:1X08_ROUND_70 |  |  |  | 
| Q1, Q2 | 2 | BSS138 | MOSFET-NWIDE | working:SOT23-WIDE |  |  |  | 
| R1, R2, R3, R4, R5, R8 | 6 | 10K | RESISTOR0805_NOOUTLINE | working:0805-NO |  |  |  | 
| U1 | 1 | LIS3DHTR | ACCEL_LIS3DHTR | working:LGA16_3X3MM |  |  |  | 
| U2 | 1 | MIC5225-3.3 | VREG_SOT23-5 | working:SOT23-5 |  |  |  | 
| U$10, U$13 | 2 | MOUNTINGHOLE2.5 | MOUNTINGHOLE2.5 | working:MOUNTINGHOLE_2.5_PLATED |  |  |  | 

## mounting_holes
| x | y | package | value | ref | size | 
| --- | --- | --- | --- | --- | --- | 
| 0.0 | 0.0 | MOUNTINGHOLE_2.5_PLATED | MOUNTINGHOLE2.5 | U$10 | m3 | 
| 15.24 | 0.0 | MOUNTINGHOLE_2.5_PLATED | MOUNTINGHOLE2.5 | U$13 | m3 |

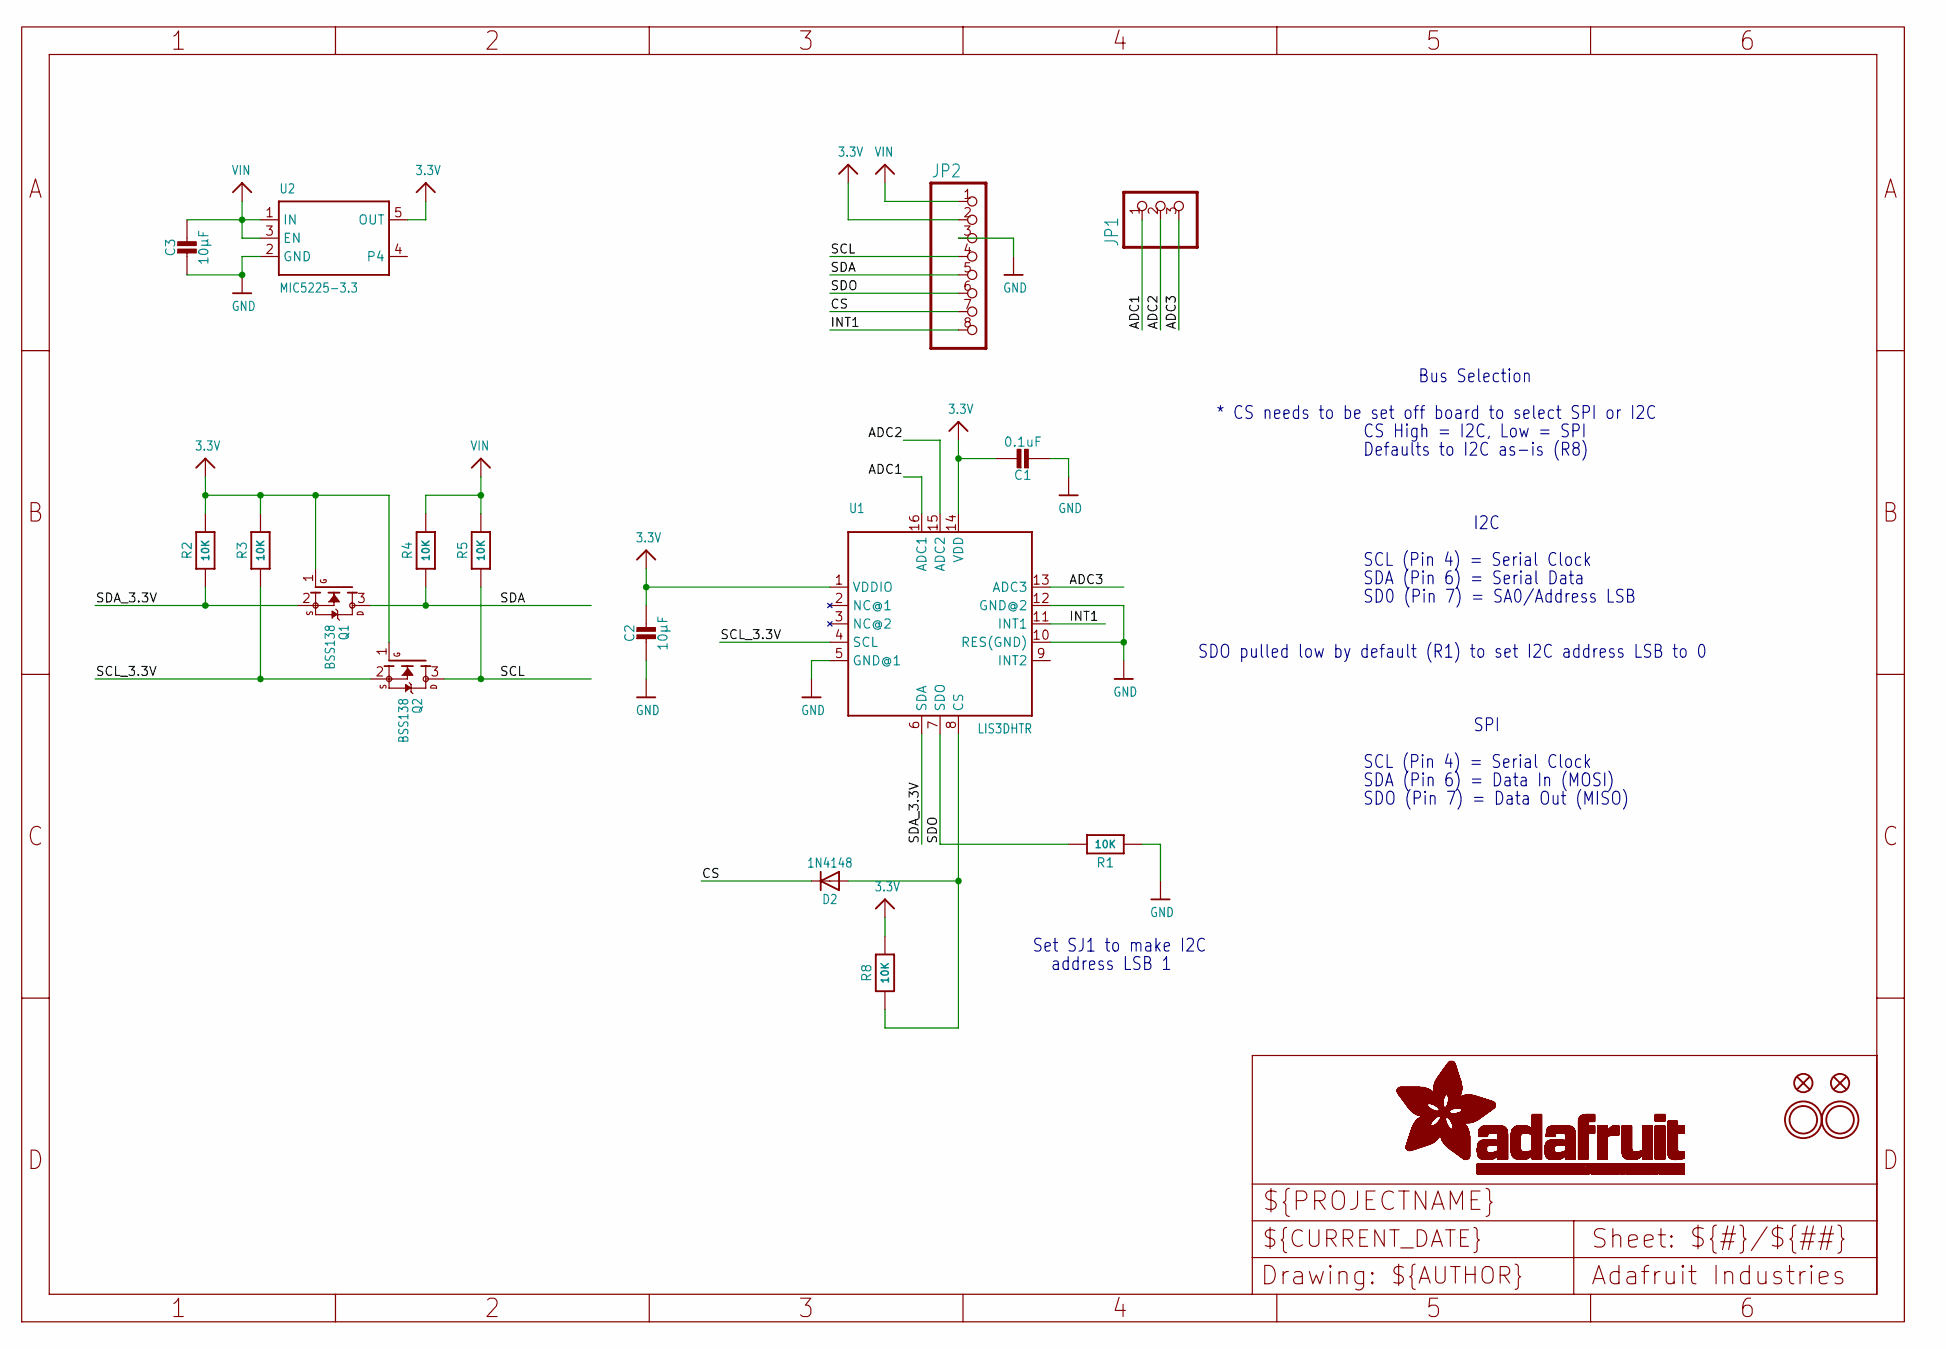
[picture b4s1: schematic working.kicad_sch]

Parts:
C1: 0.1uF; 0805_10MGAP
C2, C3: 10µF; 0805-NO
D2: 1N4148; SOD-323
FID1, FID2: FIDUCIAL""; FIDUCIAL_1MM
JP1: HEADER-1X3ROUND; 1X03_ROUND
JP2: HEADER-1X870MIL; 1X08_ROUND_70
Q1, Q2: BSS138; SOT23-WIDE
R1, R2, R3, R4, R5, R8: 10K; 0805-NO
U1: LIS3DHTR; LGA16_3X3MM
U2: MIC5225-3.3; SOT23-5
U$10, U$13: MOUNTINGHOLE2.5; MOUNTINGHOLE_2.5_PLATED

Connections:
3.3V: C1.1, C2.1, JP2.2, Q1.1 (G), Q2.1 (G), R2.2, R3.2, R8.2, U1.1 (VDDIO), U1.14 (VDD), U2.5 (OUT)
ADC1: JP1.1, U1.16 (ADC1)
ADC2: JP1.2, U1.15 (ADC2)
ADC3: JP1.3, U1.13 (ADC3)
CS: D2.C, JP2.7
GND: C1.2, C2.2, C3.2, JP2.3, R1.1, U1.5 (GND@1), U1.10 (RES(GND)), U1.12 (GND@2), U2.2 (GND)
INT1: JP2.8, U1.11 (INT1)
unnamed: D2.A, R8.1, U1.8 (CS)
SCL: JP2.4, Q2.3 (D), R5.1
SCL_3.3V: Q2.2 (S), R3.1, U1.4 (SCL)
SDA: JP2.5, Q1.3 (D), R4.1
SDA_3.3V: Q1.2 (S), R2.1, U1.6 (SDA)
SDO: JP2.6, R1.2, U1.7 (SDO)
VIN: C3.1, JP2.1, R4.2, R5.2, U2.1 (IN), U2.3 (EN)

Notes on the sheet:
SPI
Bus Selection
SCL (Pin 4) = Serial Clock
SDO (Pin 7) = Data Out (MISO)
SDO pulled low by default (R1) to set I2C address LSB to 0
* CS needs to be set off board to select SPI or I2C
SDA (Pin 6) = Serial Data
I2C
SDA (Pin 6) = Data In (MOSI)
CS High = I2C, Low = SPI
address LSB 1
Defaults to I2C as-is (R8)
SD0 (Pin 7) = SA0/Address LSB
Set SJ1 to make I2C

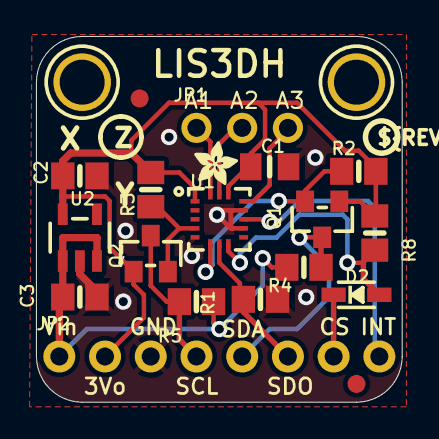
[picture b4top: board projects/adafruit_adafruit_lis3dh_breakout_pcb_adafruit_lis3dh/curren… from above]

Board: 2 copper layers, 20.3 x 20.3 mm, 23 parts (1 on the bottom side), 14 nets.

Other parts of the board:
U$9: PCBFEAT-REV-040
U$21: ADAFRUIT_2.5MM
U$22: ADAFRUIT_5MM
